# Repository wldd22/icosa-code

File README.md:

# Icosa Code

A pocket-sized Morse Code decoder with a button and LEDs.

## Details
PCB made in **KiCad**<br>
Firmware in **CircuitPython**

**Components**:
- **Seeed Studio XIAO RP2040**: Microcontroller
- **Neopixel WS2812B (5050 SMD)**: LEDs
- **6x6x5mm Tactile Push Button Switch**: Push Buttons

**Features**:
- Live **Morse Code decoding** on the LED graph
- **Status indicator** LED
- **Record and replay functionality** with two buttons

## About
Inspired by the [nux Morse Code Card Pro](https://nux-modellbau.de/en/g41731.2/nux-morse-code-card-pro),
this project is an open-source Morse Code decoder, originally made for week 5 of
Hack Club's Half Life. It has a graph where the nodes are LEDs representing letters
and the edges show dots and dashes.

The LED graph is arranged as a grid, fit inside a regular octagon. The microcontroller,
status LED, and record/play buttons are on the back of the board, surrounded by a message
in Morse Code on the silkscreen, with an icosahedron in the middle.

## Images

### Schematic

### PCB

| Complete | Copper Routing | Silkscreen Graphics |
| - | - | - |
|  |  |  |

### Board

| Front | Back |
| - | - |
|  |  |

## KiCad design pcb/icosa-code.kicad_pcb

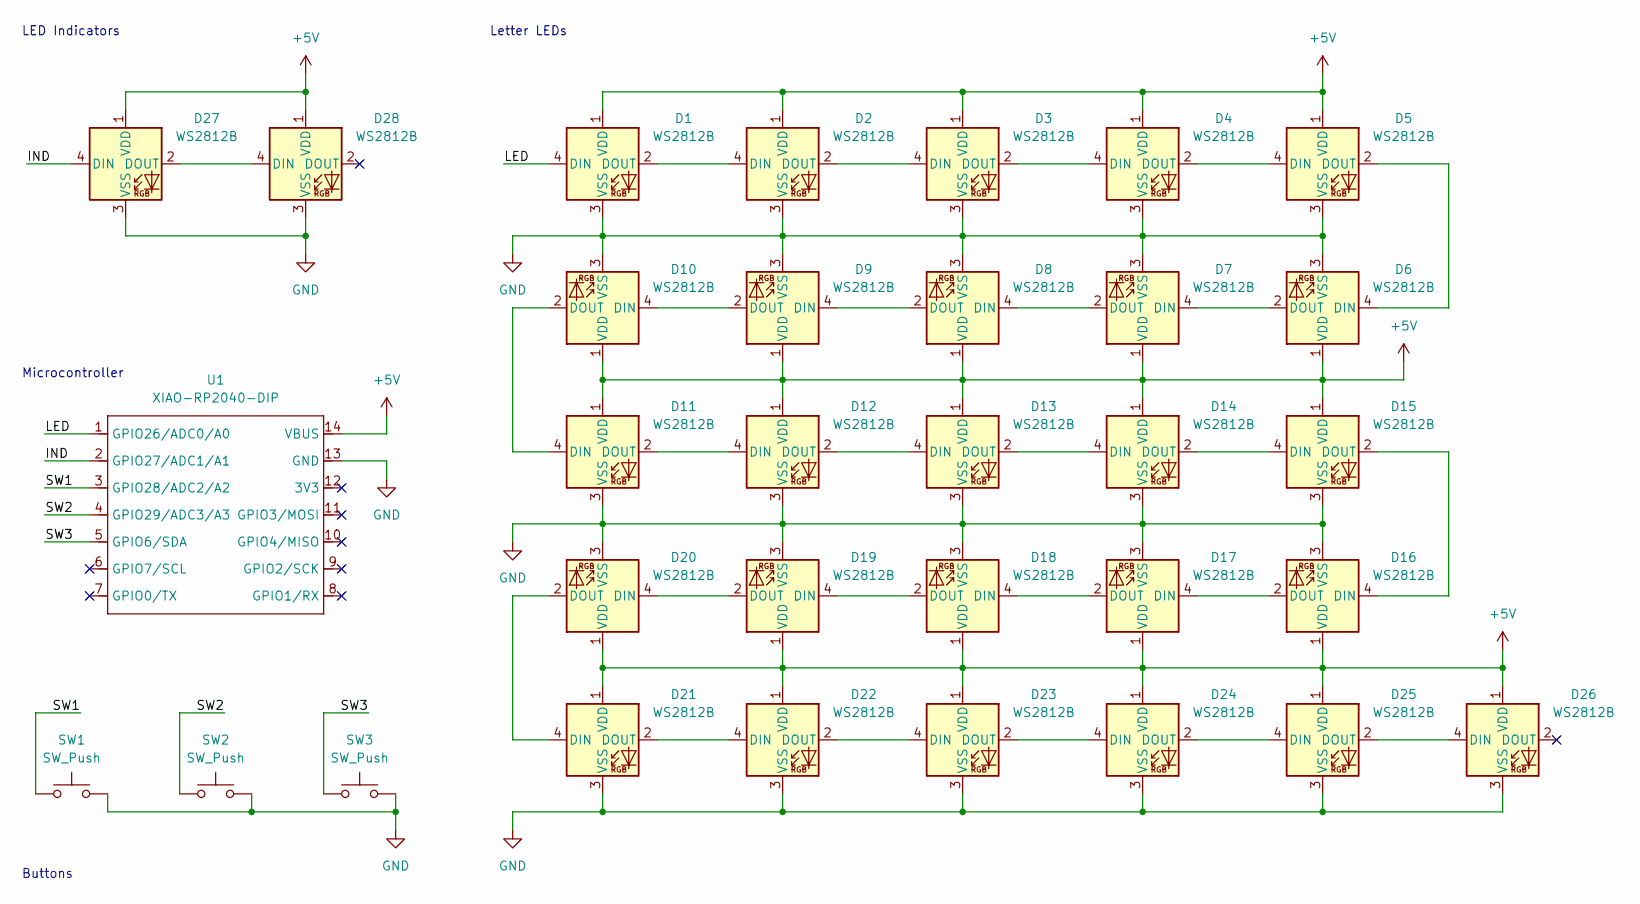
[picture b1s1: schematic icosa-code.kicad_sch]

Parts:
D1, D2, D3, D4, D5, D6, D7, D8, D9, D10, D11, D12, D13, D14, D15, D16, D17, D18, D19, D20, D21, D22, D23, D24, D25, D26, D27, D28: WS2812B; LED_WS2812B_PLCC4_5.0x5.0mm_P3.2mm
SW1, SW2, SW3: SW_Push; SW_PUSH_6mm_H5mm
U1: XIAO-RP2040-DIP

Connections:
+5V: D1.1 (VDD), D2.1 (VDD), D3.1 (VDD), D4.1 (VDD), D5.1 (VDD), D6.1 (VDD), D7.1 (VDD), D8.1 (VDD), D9.1 (VDD), D10.1 (VDD), D11.1 (VDD), D12.1 (VDD), D13.1 (VDD), D14.1 (VDD), D15.1 (VDD), D16.1 (VDD), D17.1 (VDD), D18.1 (VDD), D19.1 (VDD), D20.1 (VDD), D21.1 (VDD), D22.1 (VDD), D23.1 (VDD), D24.1 (VDD), D25.1 (VDD), D26.1 (VDD), D27.1 (VDD), D28.1 (VDD), U1.14 (VBUS)
/IND: D27.4 (DIN), U1.2 (GPIO27/ADC1/A1)
/LED: D1.4 (DIN), U1.1 (GPIO26/ADC0/A0)
/SW1: SW1.1, U1.3 (GPIO28/ADC2/A2)
/SW2: SW2.1, U1.4 (GPIO29/ADC3/A3)
/SW3: SW3.1, U1.5 (GPIO6/SDA)
GND: D1.3 (VSS), D2.3 (VSS), D3.3 (VSS), D4.3 (VSS), D5.3 (VSS), D6.3 (VSS), D7.3 (VSS), D8.3 (VSS), D9.3 (VSS), D10.3 (VSS), D11.3 (VSS), D12.3 (VSS), D13.3 (VSS), D14.3 (VSS), D15.3 (VSS), D16.3 (VSS), D17.3 (VSS), D18.3 (VSS), D19.3 (VSS), D20.3 (VSS), D21.3 (VSS), D22.3 (VSS), D23.3 (VSS), D24.3 (VSS), D25.3 (VSS), D26.3 (VSS), D27.3 (VSS), D28.3 (VSS), SW1.2, SW2.2, SW3.2, U1.13 (GND)
unnamed: D1.2 (DOUT), D2.4 (DIN)
unnamed: D2.2 (DOUT), D3.4 (DIN)
unnamed: D3.2 (DOUT), D4.4 (DIN)
unnamed: D4.2 (DOUT), D5.4 (DIN)
unnamed: D5.2 (DOUT), D6.4 (DIN)
unnamed: D6.2 (DOUT), D7.4 (DIN)
unnamed: D7.2 (DOUT), D8.4 (DIN)
unnamed: D8.2 (DOUT), D9.4 (DIN)
unnamed: D9.2 (DOUT), D10.4 (DIN)
unnamed: D10.2 (DOUT), D11.4 (DIN)
unnamed: D11.2 (DOUT), D12.4 (DIN)
unnamed: D12.2 (DOUT), D13.4 (DIN)
unnamed: D13.2 (DOUT), D14.4 (DIN)
unnamed: D14.2 (DOUT), D15.4 (DIN)
unnamed: D15.2 (DOUT), D16.4 (DIN)
unnamed: D16.2 (DOUT), D17.4 (DIN)
unnamed: D17.2 (DOUT), D18.4 (DIN)
unnamed: D18.2 (DOUT), D19.4 (DIN)
unnamed: D19.2 (DOUT), D20.4 (DIN)
unnamed: D20.2 (DOUT), D21.4 (DIN)
unnamed: D21.2 (DOUT), D22.4 (DIN)
unnamed: D22.2 (DOUT), D23.4 (DIN)
unnamed: D23.2 (DOUT), D24.4 (DIN)
unnamed: D24.2 (DOUT), D25.4 (DIN)
unnamed: D25.2 (DOUT), D26.4 (DIN)
unnamed: D27.2 (DOUT), D28.4 (DIN)

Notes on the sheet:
Microcontroller
LED Indicators
Buttons
Letter LEDs

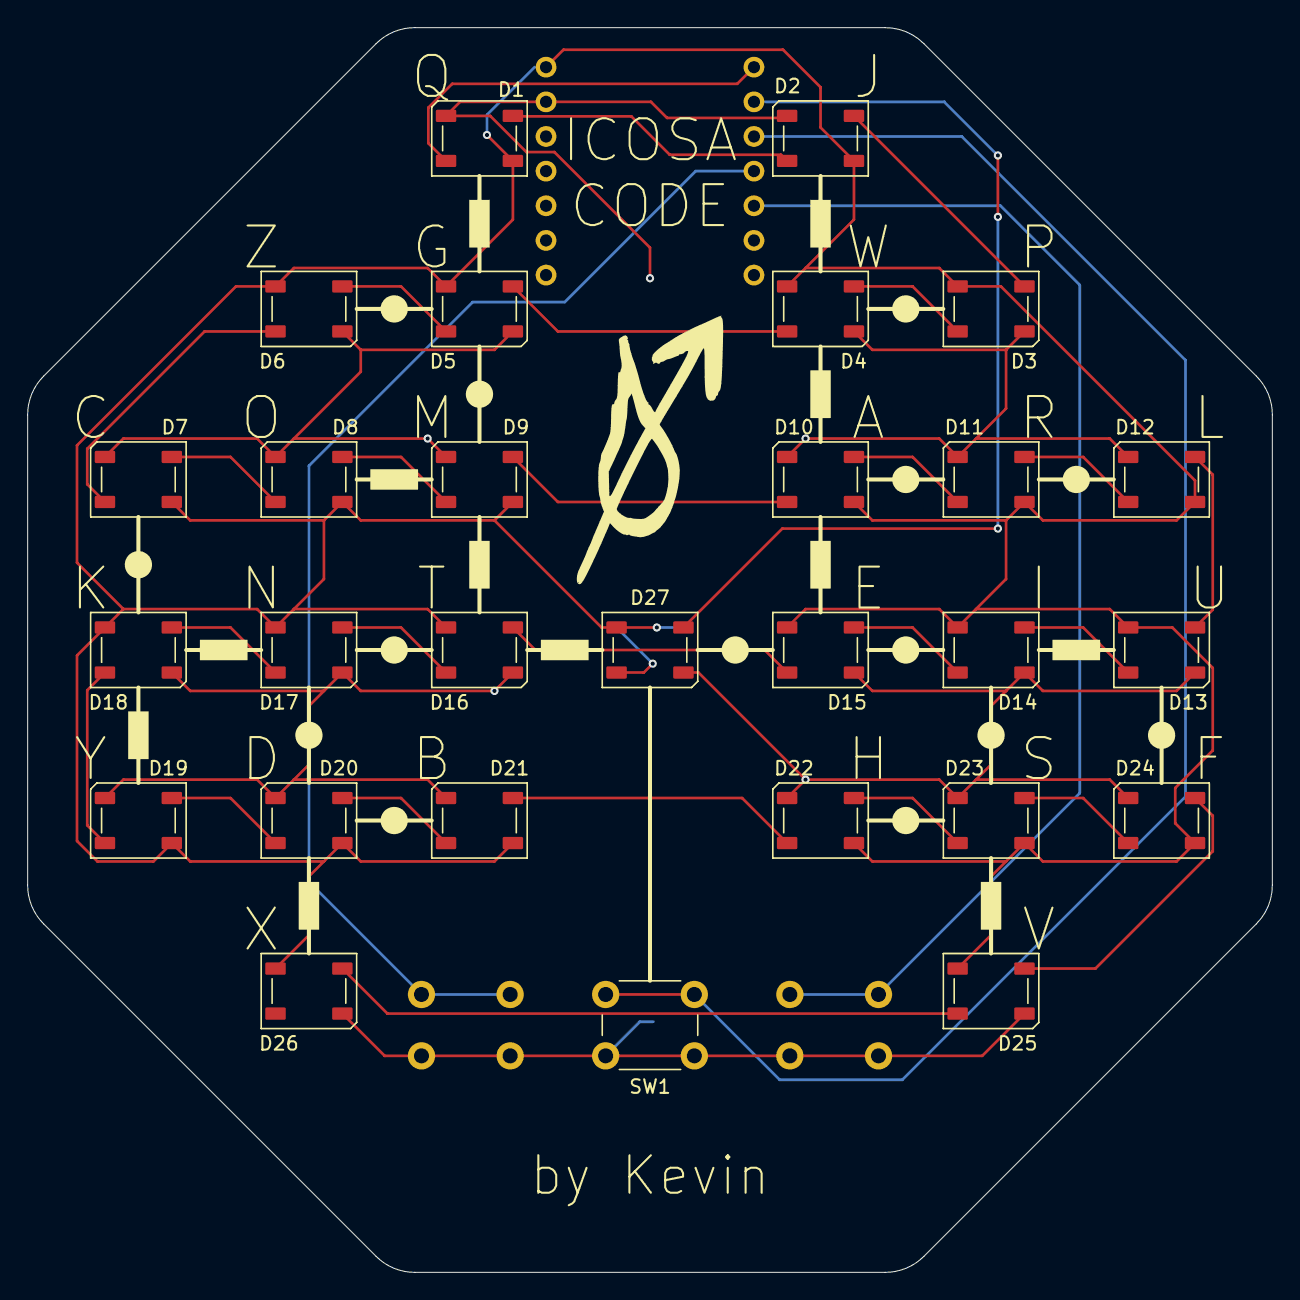
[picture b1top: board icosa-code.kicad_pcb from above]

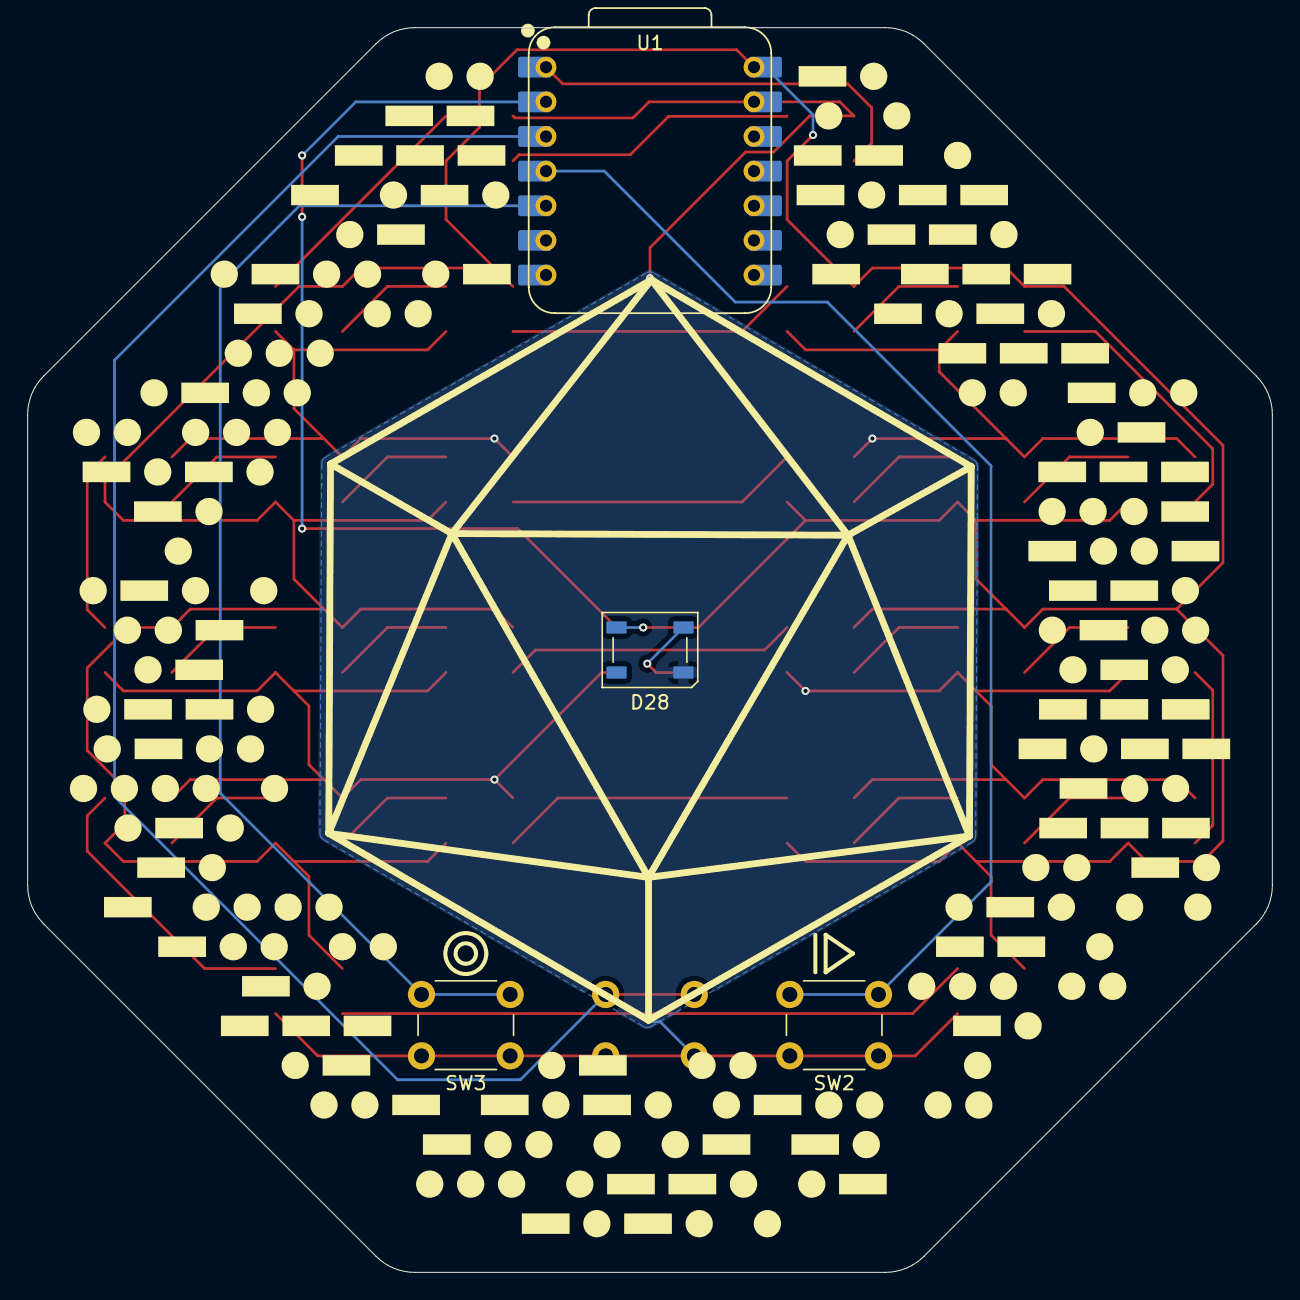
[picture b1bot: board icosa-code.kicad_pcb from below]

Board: 2 copper layers, 91.2 x 91.2 mm, 32 parts (4 on the bottom side), 33 nets.
